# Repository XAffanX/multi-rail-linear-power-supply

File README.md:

# Multi-Rail Linear Power Supply

A bench power supply with fixed **+12 V, +5 V, −12 V and −5 V** rails plus an
**adjustable LM317 output**, designed in KiCad 10. The schematic is complete and
the two-layer PCB is placed and routed with a clean DRC.

> **Project status: layout complete, not fabricated.** ERC and DRC pass,
> with no unconnected nets and no schematic/PCB mismatches. The board has not
> been ordered or tested. See [Remaining work](#remaining-work).

## Overview

Analogue bench work needs a split supply: op-amp circuits want symmetric ±12 V,
logic wants 5 V, and general prototyping wants an adjustable rail. This design
produces all of them from one centre-tapped transformer using linear regulators,
chosen over a switching topology for low output noise.

## Schematic

| Stage | Parts | Function |
|---|---|---|
| Input | J1 screw terminal | Centre-tapped transformer secondary (CT = ground) |
| Rectification | D1, KBU6M 6 A bridge | Full-wave rectification to ± raw DC |
| Bulk filtering | C7, C12, 2200 µF | One per raw rail, smooths rectifier ripple |
| +12 V | U1, LM7812 | Fed from + raw |
| +5 V | U2, LM7805 | Fed from the +12 V output |
| −12 V | U3, LM7912 | Fed from − raw |
| −5 V | U4, LM7905 | Fed from the −12 V output |
| Adjustable | U5, LM317; R1 = 470 Ω; R2 = 10 k trimmer | Adjustable output |
| Decoupling | 100 nF + 10 µF on each regulator output | Stability and HF bypass |
| Outputs | J3 (+12, +5, GND), J2 (−12, −5, ADJ, raw +) | Screw terminals |
| Extras | J4 fan header, J5 fan switch, J6 panel voltmeter | Cooling and monitoring |

### Adjustable rail range

The LM317 holds 1.25 V across R1, and R2 sets the output:

```
Vout = 1.25 × (1 + R2/R1)
     = 1.25 V (R2 = 0)  to  1.25 × (1 + 10000/470) ≈ 27.8 V (R2 = 10 k)
```

In practice the maximum is limited by the input: the LM317 needs about 3 V of
headroom, so the output can only reach roughly 3 V below the + raw rail.

### Design decisions

- **Cascaded 5 V regulators.** The 7805 and 7905 run from the ±12 V outputs
  rather than from the raw rails, splitting the voltage drop (and heat) across
  two packages.
- **Two-tier decoupling.** 2200 µF bulk capacitors handle rectifier ripple;
  10 µF and 100 nF capacitors at each regulator output handle stability and
  high-frequency bypass.
- **6 A bridge.** KBU6M is rated well above the expected draw, giving headroom
  and lower junction temperature.

## PCB

*Left: top copper and silkscreen. Right: bottom copper.*

- **Board:** 130 × 88 mm, two layers, four M3 mounting holes.
- **Flow:** AC input and bridge on the left. Positive regulators along the top
  edge and negative regulators in the lower half, each with about 12 mm of
  clear space behind its tab for a heatsink. Output terminals on the right
  edge, with wire entries facing out.
- **Copper:** ground planes on both layers with stitching vias. 1.5 mm power
  tracks; only a few short tracks on the bottom layer.
- **Footprints:** all through-hole: TO-220 regulators, radial electrolytics,
  Phoenix MKDS 5.08 mm terminal blocks, and a Bourns 3296W trimmer.

**Heatsink warning:** the regulator tabs are at different potentials (GND on
the 78xx, the input on the 79xx, the output on the LM317). Use a separate
heatsink for each, or insulating pads and washers on a shared one.

## How to Open

1. Install [KiCad 10](https://www.kicad.org/download/).
2. Open `hardware/LinearPowerSupply.kicad_pro`.
3. The schematic opens in Eeschema and the routed board in Pcbnew.

## Remaining Work

1. **Choose the transformer.** Its secondary voltage sets the raw rails,
   regulator dissipation and the LM317's maximum output.
2. **Thermal calculation.** For each regulator, dissipation is
   `(Vin − Vout) × Iout`; size the heatsinks from that.
3. **Protection.** Add an input fuse and bleeder resistors across the bulk
   capacitors.
4. **Generate Gerbers and a BOM**, order boards, build, and test.

## Repository Structure

```
.
├── hardware/
│   ├── LinearPowerSupply.kicad_pro   project file
│   ├── LinearPowerSupply.kicad_sch   schematic
│   └── LinearPowerSupply.kicad_pcb   routed PCB
├── images/
│   ├── 01-schematic.png              schematic export
│   ├── 02-pcb-layout.png             top and bottom copper
│   └── 03-pcb-3d.png                 3D render
└── README.md
```

> **Safety note.** This design rectifies an AC input. The transformer secondary
> and bulk capacitors hold dangerous energy. Do not build it without fusing,
> an enclosure and appropriate precautions.

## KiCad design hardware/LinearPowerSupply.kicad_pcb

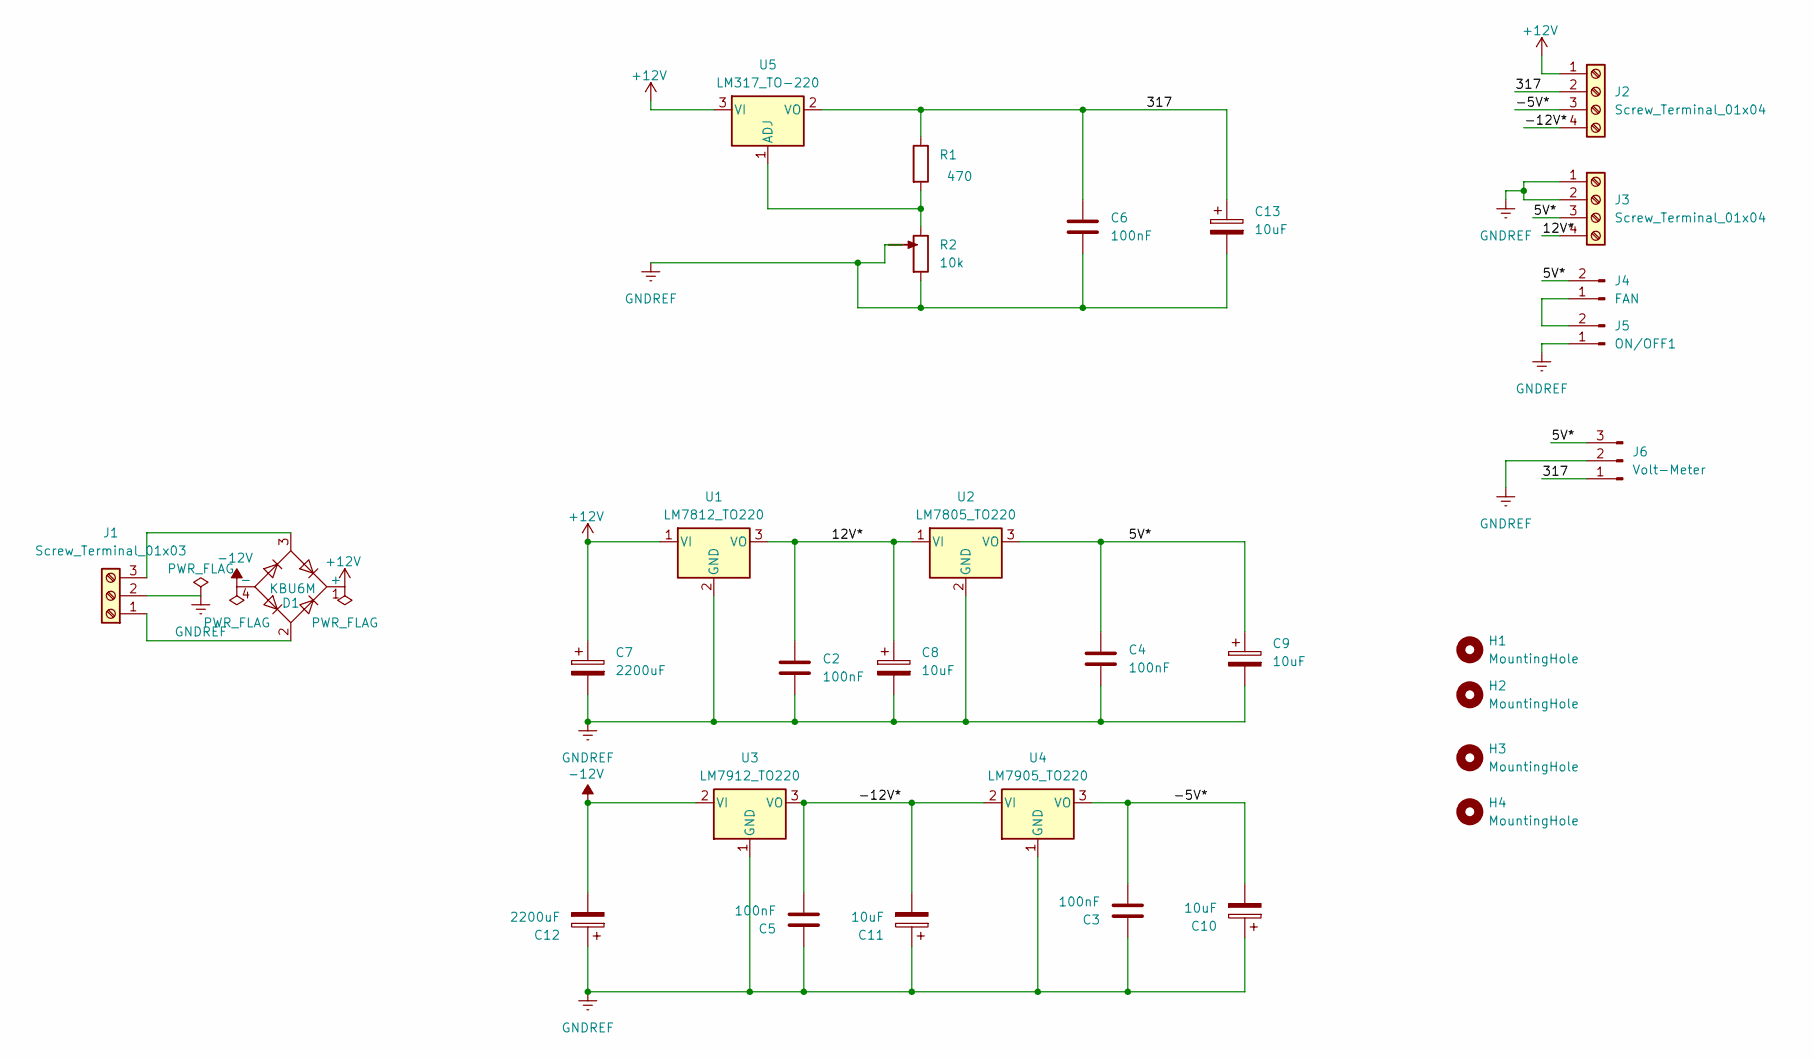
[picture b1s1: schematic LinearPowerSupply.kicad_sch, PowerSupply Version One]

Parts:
C2, C3, C4, C5, C6: 100nF; C_Disc_D5.0mm_W2.5mm_P5.00mm
C7, C12: 2200uF; CP_Radial_D12.5mm_P5.00mm
C8, C9, C10, C11, C13: 10uF; CP_Radial_D5.0mm_P2.00mm
D1: KBU6M; Diode_Bridge_Vishay_KBU
H1, H2, H3, H4: MountingHole; MountingHole_3.2mm_M3
J1: Screw_Terminal_01x03; TerminalBlock_Phoenix_MKDS-1,5-3-5.08_1x03_P5.08mm_Horizont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
J2, J3: Screw_Terminal_01x04; TerminalBlock_Phoenix_MKDS-1,5-4-5.08_1x04_P5.08mm_Horizont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
J4: FAN; PinHeader_1x02_P2.54mm_Vertical
J5: ON/OFF1; TerminalBlock_Phoenix_MKDS-1,5-2-5.08_1x02_P5.08mm_Horizont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
J6: Volt-Meter; PinHeader_1x03_P2.54mm_Vertical
R1: 470; R_Axial_DIN0207_L6.3mm_D2.5mm_P10.16mm_Horizontal
R2: 10k; Potentiometer_Bourns_3296W_Vertical
U1: LM7812_TO220; TO-220-3_Vertical
U2: LM7805_TO220; TO-220-3_Vertical
U3: LM7912_TO220; TO-220-3_Vertical
U4: LM7905_TO220; TO-220-3_Vertical
U5: LM317_TO-220; TO-220-3_Vertical

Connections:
+12V: C7.1, D1.1 (+), J2.1, U1.1 (VI), U5.3 (VI)
-12V: C12.2, D1.4 (-), U3.2 (VI)
/5V*: C4.1, C9.1, J3.3, J4.2, J6.3, U2.3 (VO)
/12V*: C2.1, C8.1, J3.4, U1.3 (VO), U2.1 (VI)
/317: C6.1, C13.1, J2.2, J6.1, R1.1, U5.2 (VO)
/-5V*: C3.2, C10.2, J2.3, U4.3 (VO)
/-12V*: C5.2, C11.2, J2.4, U3.3 (VO), U4.2 (VI)
GNDREF: C2.2, C3.1, C4.2, C5.1, C6.2, C7.2, C8.2, C9.2, C10.1, C11.1, C12.1, C13.2, J1.2, J3.1, J3.2, J5.1, J6.2, R2.2, U1.2 (GND), U2.2 (GND), U3.1 (GND), U4.1 (GND)
unnamed: D1.2, J1.1
unnamed: D1.3, J1.3
unnamed: J4.1, J5.2
unnamed: R1.2, R2.1, U5.1 (ADJ)

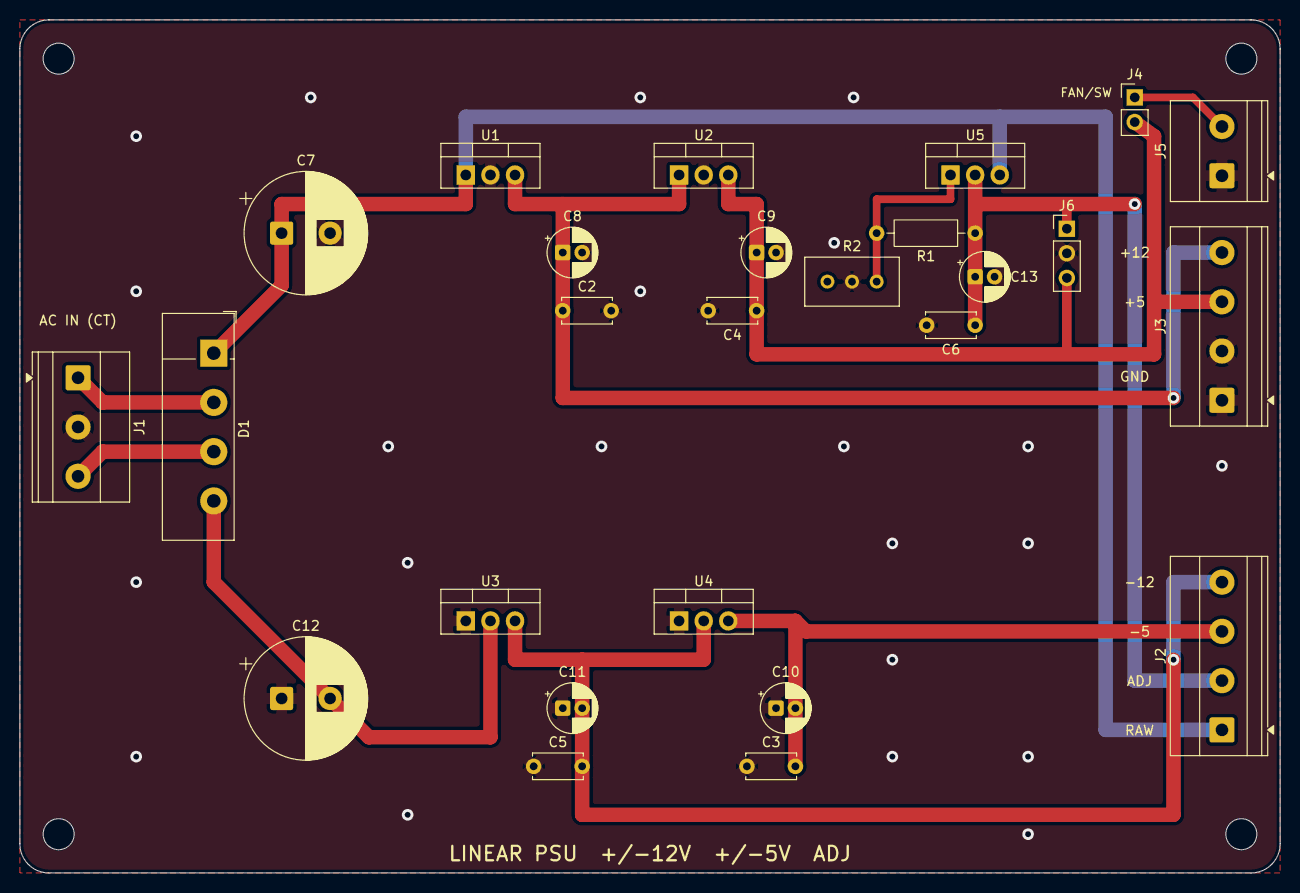
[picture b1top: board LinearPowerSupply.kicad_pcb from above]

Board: 2 copper layers, 130.0 x 88.0 mm, 30 parts (0 on the bottom side), 12 nets.
